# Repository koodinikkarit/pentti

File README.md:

# Pentti on ohjelmisto arduinolle jolla lähetetään napin painallukset serverille.

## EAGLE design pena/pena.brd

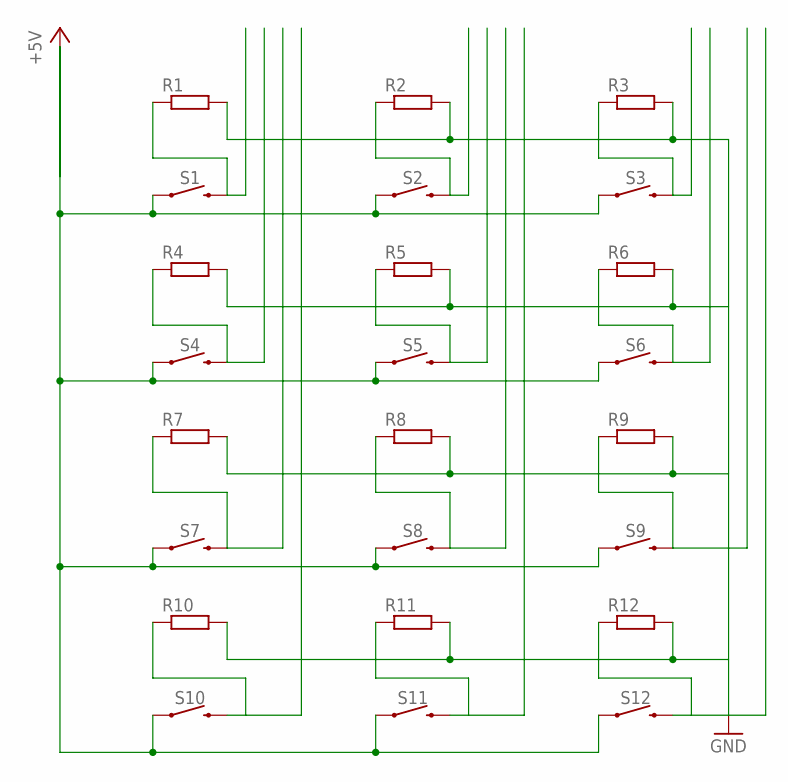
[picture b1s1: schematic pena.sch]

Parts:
R1, R2, R3, R4, R5, R6, R7, R8, R9, R10, R11, R12: R-EU_0207/10; 0207/10
S1, S2, S3, S4, S5, S6, S7, S8, S9, S10, S11, S12: MOMENTARY-SWITCH-SPST-SMD-6.2MM-TALL; TACTILE_SWITCH_SMD_6.2MM_TALL

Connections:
+5V: S1.A2 (1), S2.A2 (1), S3.A2 (1), S4.A2 (1), S5.A2 (1), S6.A2 (1), S7.A2 (1), S8.A2 (1), S9.A2 (1), S10.A2 (1), S11.A2 (1), S12.A2 (1)
GND: R1.2, R2.2, R3.2, R4.2, R5.2, R6.2, R7.2, R8.2, R9.2, R10.2, R11.2, R12.2
unnamed: R1.1, S1.B2 (2)
unnamed: R12.1, S12.B2 (2)
unnamed: R11.1, S11.B2 (2)
unnamed: R10.1, S10.B2 (2)
unnamed: R2.1, S2.B2 (2)
unnamed: R3.1, S3.B2 (2)
unnamed: R4.1, S4.B2 (2)
unnamed: R9.1, S9.B2 (2)
unnamed: R8.1, S8.B2 (2)
unnamed: R7.1, S7.B2 (2)
unnamed: R5.1, S5.B2 (2)
unnamed: R6.1, S6.B2 (2)

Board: 2 copper layers, 24 parts (0 on the bottom side), 14 nets, no tracks yet.

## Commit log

2016-12-02 Add .gitignore and .gitattributes.
2016-12-02 Add project files.
2016-12-15 Nappien muutokset lähetetään serverille.
2017-01-21 Luotu pentille pcb piirustus.
2017-02-01 Poistetu eagle ja luotu README.md
2017-02-08 Poistettu visualstudio ja lisätty atmeli.
2017-02-14 Luotu pentistä uusi versio.

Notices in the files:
parts and their libraries:
SparkFun-Switches: Licensing: Creative Commons ShareAlike 4.0 International - https://creativecommons.org/licenses/by-sa/4.0
